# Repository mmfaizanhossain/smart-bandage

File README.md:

# Smart Bandage: Real-Time Wound Monitoring and Vibration Therapy

A wearable, rechargeable smart bandage that streams wound-site **temperature and humidity** to a phone over **Bluetooth Low Energy** and drives **low-frequency vibration motors** for mechanotherapy. It is built on a **Seeed XIAO nRF52840** (Nordic nRF52840, Arm Cortex-M4F, BLE 5.0).

This project is published as a first-author paper at **IEEE GCCE 2025** ([DOI: 10.1109/GCCE65946.2025.11275449](https://doi.org/10.1109/GCCE65946.2025.11275449)): *"From Skin to Screen: Real-Time Wound Monitoring with a Smart Bandage and Smartphone."* (Citation below.)

▶ **[Demo video](docs/media/demo.mp4)**

## System overview

The device has two parts:

- **A reusable electronics module** in a 3D-printed TPU case. It contains the MCU, the sensor, the motor driver and the battery.
- **A disposable adhesive wound-contact patch** that snap-fits to the module, so only the cheap part is thrown away.

| Subsystem | Implementation |
|---|---|
| MCU / radio | Seeed XIAO nRF52840 (BLE 5.0, Bluefruit stack) |
| Sensing | Sensirion SHT31-D over I²C at 0x44 (±0.3 °C, ±2 % RH) |
| Therapy | 2× coin vibration motors (Seeed 316040001), 45–60 Hz |
| Motor driver | Low-side N-MOSFET (SI2300), 1N5817 flyback diode, pull-down resistor |
| Power | 3.7 V 200 mAh Li-Po, USB-C charging |
| App | iOS (Swift): live readings, alerts, history graph, therapy on/off |

## Firmware

The production sketch is [`firmware/smart_bandage/smart_bandage.ino`](firmware/smart_bandage/smart_bandage.ino).

- **BLE UART (Nordic UART Service).** The device advertises as `Smart Bandage` and sends `"<temp>,<humidity>\n"` at **1 Hz**.
- **App commands.** `ON` / `OFF` sent over BLE UART switch the motor PWM (50 Hz, 50 % duty) through the MOSFET on pin D6.
- **Low power.** Between samples the CPU sleeps in `sd_app_evt_wait()` (SoftDevice event wait) instead of busy-looping. Sensor strings use stack buffers rather than `String`, which avoids heap fragmentation.
- **Debug switch.** Setting `#define DEBUG 0` strips all serial logging for production builds.

### Development history (`firmware/archive/`)

| Sketch | Stage | What it tested |
|---|---|---|
| `s1_nfc_sensor_logger` | Stage 1 | XIAO RP2040 + PN532: SHT31 readings written to an NFC tag |
| `s2a_ble_sensor_stream` | Stage 2 | Moved to nRF52840; streams SHT31 data over BLE UART |
| `s2b_motor_test` | Stage 2 | Motor on/off timing test |
| `s2c_ble_pwm_combined` | Stage 2 | BLE streaming and 2 s on/off PWM vibration together |
| `s2d_low_power_auto_cycle` | Stage 2 | Event-driven sleep between sensor reads and motor toggles |
| `s2e_ble_motor_control` | Stage 2 | Motor controlled from the app over BLE |

Stage 1 used NFC, so a phone had to tap the bandage to read it. Switching to BLE made the readings continuous, and that change is what made remote monitoring possible.

### Build

1. Arduino IDE → **Boards Manager** → install **Seeed nRF52 Boards** and select **Seeed XIAO nRF52840**.
2. Install the libraries **Adafruit SHT31** and **nRF52_PWM** (khoih-prog).
3. Open `firmware/smart_bandage/smart_bandage.ino` and upload it.
4. Connect with any BLE UART app (for example nRF Connect or Bluefruit Connect). Send `ON\n` or `OFF\n` and watch the CSV readings arrive.

## Hardware

The KiCad 9 project is in [`hardware/kicad/`](hardware/kicad/), with the schematic, a 2-layer PCB and custom symbols and footprints for the XIAO nRF52840, the SHT3x, the motors, the N-FET and the battery.

## Results (bench tests, no human subjects)

- Sensor readings stayed within physiological wound-care ranges (20–40 °C, 40–90 % RH) under controlled heat and humidity sources.
- BLE UART streaming at 1 Hz had **latency under 200 ms** and stayed stable within **5 m** indoors.
- Motors actuated from the app responded in **under 1 s**.
- The device ran untethered on its 200 mAh battery.

## Paper

> F. M. Hossain, D. J. G. Tan, I. M. Ameer, Q. Q. Ayun, S. Matsunaga, S. A. Junaideen, and Z. Liang, "From Skin to Screen: Real-Time Wound Monitoring with a Smart Bandage and Smartphone," in *2025 IEEE 14th Global Conference on Consumer Electronics (GCCE)*, Osaka, Japan, Sep. 2025. DOI: [10.1109/GCCE65946.2025.11275449](https://doi.org/10.1109/GCCE65946.2025.11275449)

```bibtex
@inproceedings{hossain2025skin,
  title     = {From Skin to Screen: Real-Time Wound Monitoring with a Smart Bandage and Smartphone},
  author    = {Hossain, Faizan M. and Tan, Daphne Jillian Gan and Ameer, Imad Mohamed and Ayun, Queena Qurrota and Matsunaga, Suo and Junaideen, Suleiman Arif and Liang, Zilu},
  booktitle = {2025 IEEE 14th Global Conference on Consumer Electronics (GCCE)},
  address   = {Osaka, Japan},
  month     = sep,
  year      = {2025},
  publisher = {IEEE},
  doi       = {10.1109/GCCE65946.2025.11275449}
}
```

## Team

Developed at the **Ubiquitous and Personal Computing Lab, Kyoto University of Advanced Science**. Co-authors: Daphne Jillian Gan Tan, Imad Mohamed Ameer, Queena Qurrota Ayun, Suo Matsunaga, Suleiman Arif Junaideen and Zilu Liang.

**Faizan Hossain** (first author) · [LinkedIn](https://www.linkedin.com/in/faizan-hossain/)

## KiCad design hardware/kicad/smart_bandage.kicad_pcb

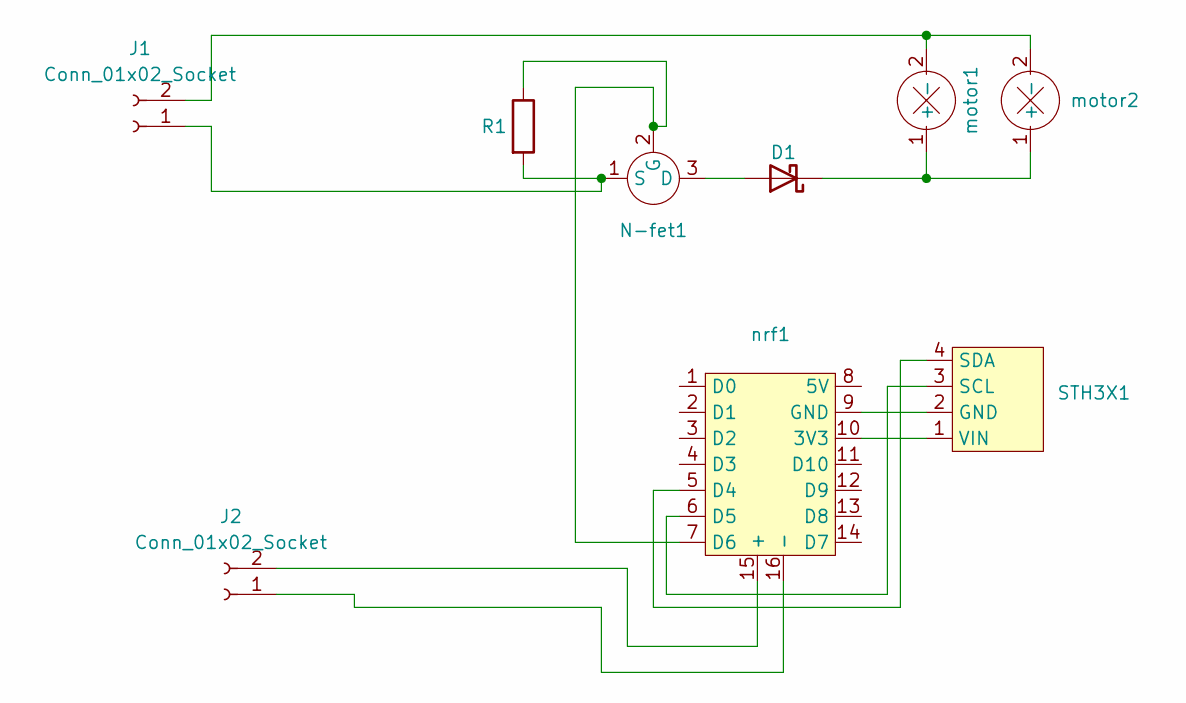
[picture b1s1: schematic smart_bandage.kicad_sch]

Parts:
D1: 1N5817; D_DO-41_SOD81_P10.16mm_Horizontal
J1, J2: Conn_01x02_Socket; JST_EH_S2B-EH_1x02_P2.50mm_Horizontal
N-fet1: N-fet
R1: R; R_Axial_DIN0204_L3.6mm_D1.6mm_P2.54mm_Vertical
STH3X1: STH3X
motor1, motor2: motor
nrf1: nrf52840

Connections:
unnamed: D1.2 (A), N-fet1.3 (D)
unnamed: D1.1 (K), motor1.1 (+), motor2.1 (+)
unnamed: J1.1, N-fet1.1 (S), R1.2
unnamed: J1.2, motor1.2 (-), motor2.2 (-)
unnamed: J2.1, nrf1.16 (-)
unnamed: J2.2, nrf1.15 (+)
unnamed: N-fet1.2 (G), R1.1, nrf1.7 (D6)
unnamed: STH3X1.2 (GND), nrf1.9 (GND)
unnamed: STH3X1.3 (SCL), nrf1.6 (D5)
unnamed: STH3X1.4 (SDA), nrf1.5 (D4)
unnamed: STH3X1.1 (VIN), nrf1.10 (3V3)

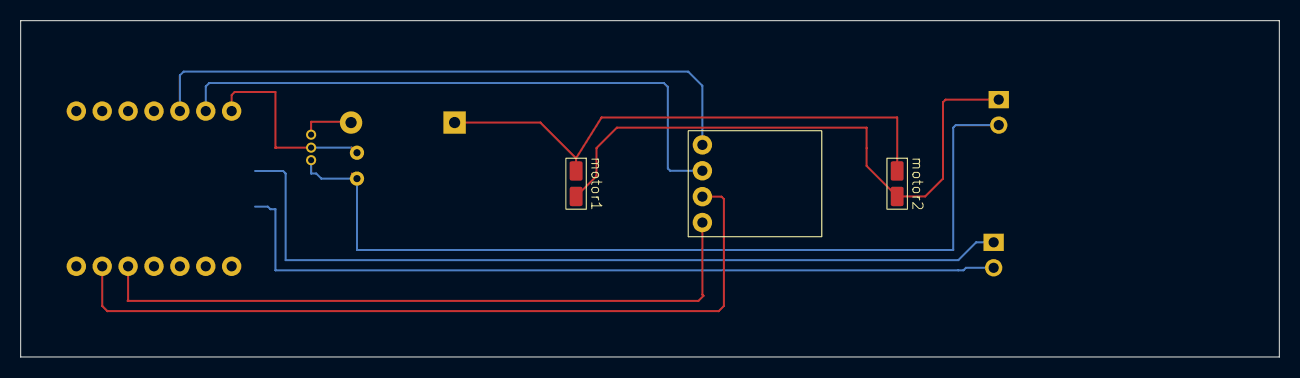
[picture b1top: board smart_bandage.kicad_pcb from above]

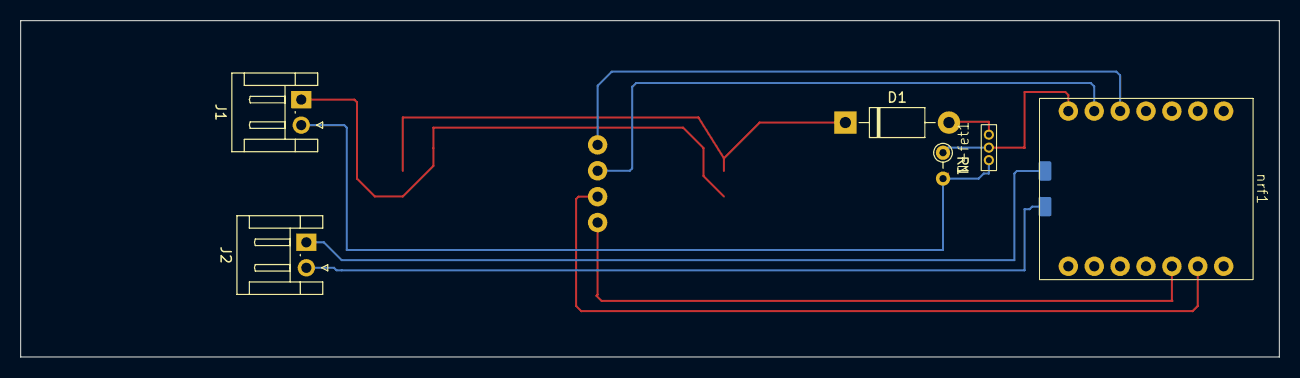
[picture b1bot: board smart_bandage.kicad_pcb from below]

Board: 2 copper layers, 123.5 x 33.0 mm, 9 parts (6 on the bottom side), 11 nets.
